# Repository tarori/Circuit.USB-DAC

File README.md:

USB Audio DAC version 10
 * Input: USB Audio class 2.0 (192kHz/24bit)
 * Output: Headphone and speakers (max 5W @8Ω)
 * THD+N < -100dB (0.001%) at 1W 8Ω 
 * Low output noise: <10uVrms (20-20kHz)
 * 4-layer PCB with solid ground
 * SDR-Widget with very low jitter design
 * Isolated USB input
 * AK4493 with AK1110 and [LED regulators](https://github.com/tarori/Circuit.LEC-Regulator) (discrete low noise, low impedance regulator) 
 * Low gain class-AB amplifier
 * Two mute relays for headphone and speakers
 * Input power: ±20V 2A

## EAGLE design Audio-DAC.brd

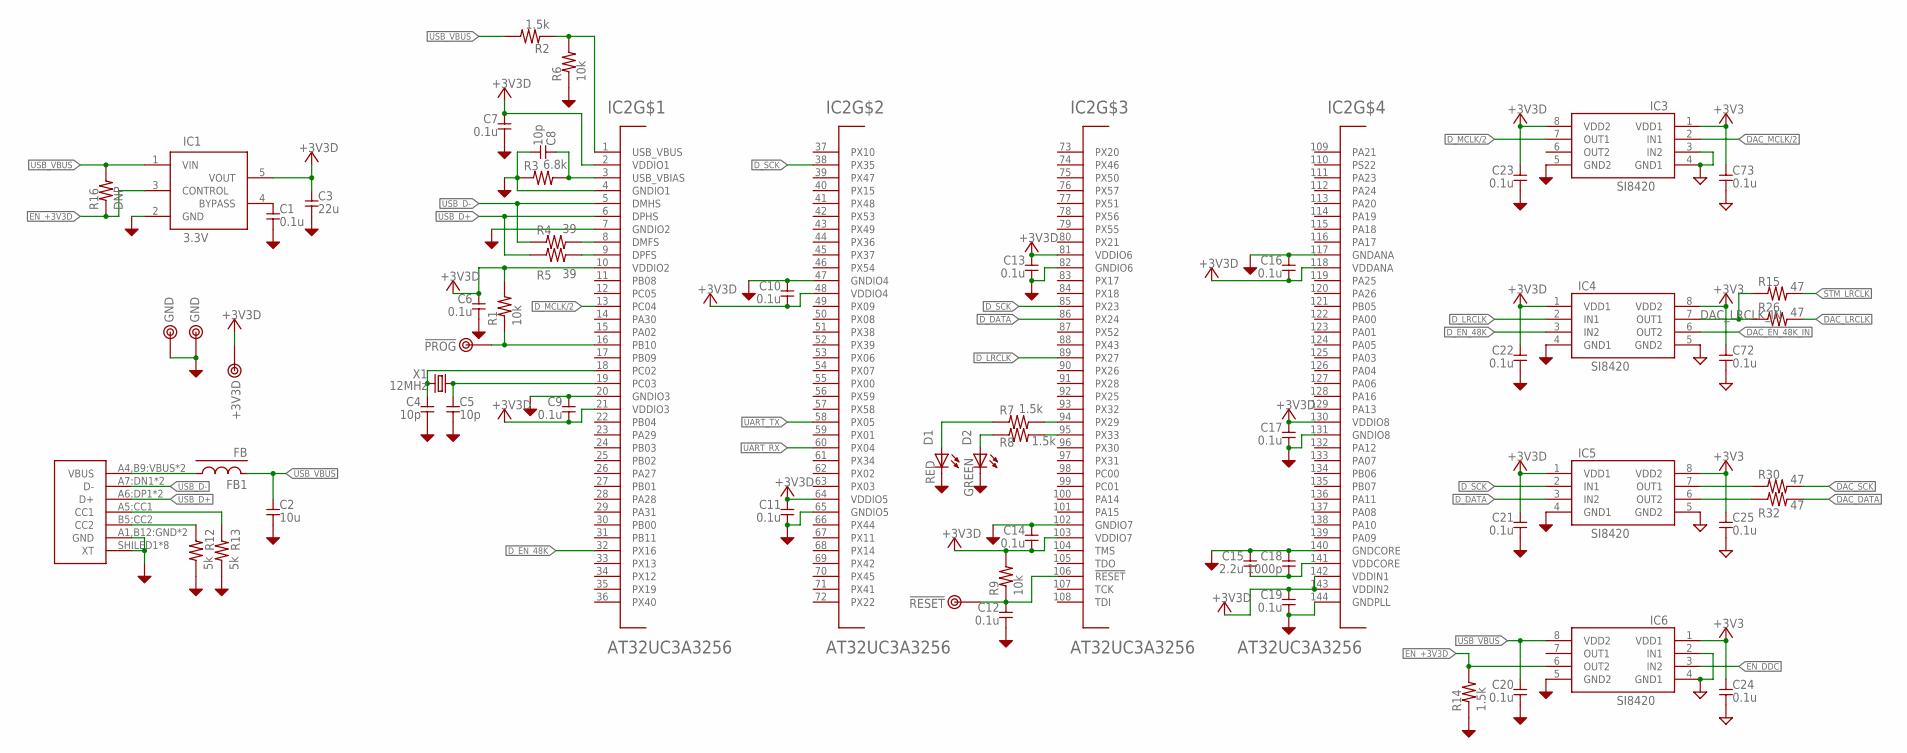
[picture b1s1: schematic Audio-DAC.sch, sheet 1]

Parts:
C1, C6, C7, C9, C10, C11, C12, C13, C14, C16, C17, C19, C20, C21, C22, C23, C24, C25, C72, C73: 0.1u; 1608C
C2: 10u; 2012
C3: 22u; 2012
C4, C5, C8: 10p; 1608C
C15: 2.2u; 2012
C18: 1000p; 1608C
CON1: USB-C; 5077CR-16-SMC2-BK-TR
D1: RED; D1608
D2: GREEN; D1608
FB1: FB; 1608-J
IC1: 3.3V; SOT23-5
IC2: AT32UC3A3256; TQFP144
IC3, IC4, IC5, IC6: SI8420; SOP8
R1, R6, R9: 10k; 1608
R2, R7, R8, R14: 1.5k; 1608
R3: 6.8k; 1608
R4, R5: 39; 1608
R12, R13: 5k; 1608
R15, R26, R30, R32: 47; 1608-J
R16: DNP; 1608-J
TP1: !PROG; TESTPIN
TP2: !RESET; TESTPIN
TP3, TP25: GND; TESTPIN
TP26: +3V3D; TESTPIN
X1: 12MHz; HC49/S

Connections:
+3V3: C24.1, C25.1, C72.1, C73.1, IC3.1 (VDD1), IC4.8 (VDD2), IC5.8 (VDD2), IC6.1 (VDD1); also elsewhere on the board
+3V3D: C3.1, C6.1, C7.1, C9.2, C10.2, C11.1, C13.1, C14.2, C16.2, C17.1, C19.1, C21.1, C22.1, C23.1, IC1.5 (VOUT), IC2.2 (VDDIO1), IC2.10 (VDDIO2), IC2.21 (VDDIO3), IC2.48 (VDDIO4), IC2.64 (VDDIO5), IC2.81 (VDDIO6), IC2.103 (VDDIO7), IC2.118 (VDDANA), IC2.130 (VDDIO8), IC2.142 (VDDIN1), IC2.143 (VDDIN2), IC3.8 (VDD2), IC4.1 (VDD1), IC5.1 (VDD1), R1.2, R9.2, TP26.1
AVR_PROG: IC2.16 (PB10), R1.1, TP1.1
DAC_DATA: R32.2; also elsewhere on the board
DAC_EN_48K_IN: IC4.6 (OUT2); also elsewhere on the board
DAC_LRCLK: R26.2; also elsewhere on the board
DAC_LRCLK_IN: IC4.7 (OUT1), R15.1, R26.1
DAC_MCLK/2: IC3.2 (IN1); also elsewhere on the board
DAC_SCK: R30.2; also elsewhere on the board
DGND: C1.2, C2.2, C3.2, C4.2, C5.2, C6.2, C7.2, C8.2, C9.1, C10.1, C11.2, C12.2, C13.2, C14.1, C15.1, C16.1, C17.2, C18.1, C19.2, C20.2, C21.2, C22.2, C23.2, CON1.A1,B12:GND (GND), CON1.B1,A12:GND (GND), CON1.SHILED1 (XT), CON1.SHILED2 (XT), CON1.SHILED3 (XT), CON1.SHILED4 (XT), CON1.SHILED5 (XT), CON1.SHILED6 (XT), CON1.SHILED7 (XT), CON1.SHILED8 (XT), D1.K, D2.K, IC1.2 (GND), IC2.4 (GNDIO1), IC2.7 (GNDIO2), IC2.20 (GNDIO3), IC2.47 (GNDIO4), IC2.65 (GNDIO5), IC2.82 (GNDIO6), IC2.102 (GNDIO7), IC2.117 (GNDANA), IC2.131 (GNDIO8), IC2.140 (GNDCORE), IC2.144 (GNDPLL), IC3.5 (GND2), IC4.4 (GND1), IC5.4 (GND1), IC6.5 (GND2), R3.1, R6.1, R12.1, R13.1, R14.1, TP3.1, TP25.1
D_!RST: C12.1, IC2.106 (!RESET), R9.1, TP2.1
D_DATA: IC2.86 (PX24), IC5.3 (IN2)
D_EN_48K: IC2.32 (PX16), IC4.3 (IN2)
D_LRCLK: IC2.89 (PX27), IC4.2 (IN1)
D_MCLK/2: IC2.13 (PC04), IC3.7 (OUT1)
D_SCK: IC2.38 (PX35), IC2.85 (PX23), IC5.2 (IN1)
EN_+3V3D: IC1.3 (CONTROL), IC6.6 (OUT2), R14.2, R16.1
EN_DDC: IC6.3 (IN2); also elsewhere on the board
GND: C24.2, C25.2, C72.2, C73.2, IC3.3 (IN2), IC3.4 (GND1), IC4.5 (GND2), IC5.5 (GND2), IC6.2 (IN1), IC6.4 (GND1); also elsewhere on the board
LED_GREEN: IC2.95 (PX33), R8.2
LED_RED: IC2.94 (PX29), R7.2
unnamed: IC2.8 (DMFS), R4.2
unnamed: IC2.9 (DPFS), R5.2
unnamed: C5.1, IC2.19 (PC03), X1.1
unnamed: C4.1, IC2.18 (PC02), X1.2
unnamed: C8.1, IC2.3 (USB_VBIAS), R3.2
unnamed: IC2.1 (USB_VBUS), R2.1, R6.2
unnamed: D2.A, R8.1
unnamed: C15.2, C18.2, IC2.141 (VDDCORE)
unnamed: D1.A, R7.1
unnamed: IC5.7 (OUT1), R30.1
unnamed: C1.1, IC1.4 (BYPASS)
unnamed: CON1.B5:CC2 (CC2), R12.2
unnamed: CON1.A5:CC1 (CC1), R13.2
unnamed: IC5.6 (OUT2), R32.1
STM_LRCLK: R15.2; also elsewhere on the board
UART_RX: IC2.60 (PX04)
UART_TX: IC2.58 (PX05)
USB_D+: CON1.A6:DP1 (D+), CON1.B6:DP2 (D+), IC2.6 (DPHS), R5.1
USB_D-: CON1.A7:DN1 (D-), CON1.B7:DN2 (D-), IC2.5 (DMHS), R4.1
USB_VBUS: C2.1, C20.1, FB1.2, IC1.1 (VIN), IC6.8 (VDD2), R2.2, R16.2
VBUS: CON1.A4,B9:VBUS (VBUS), CON1.B4,A9:VBUS (VBUS), FB1.1

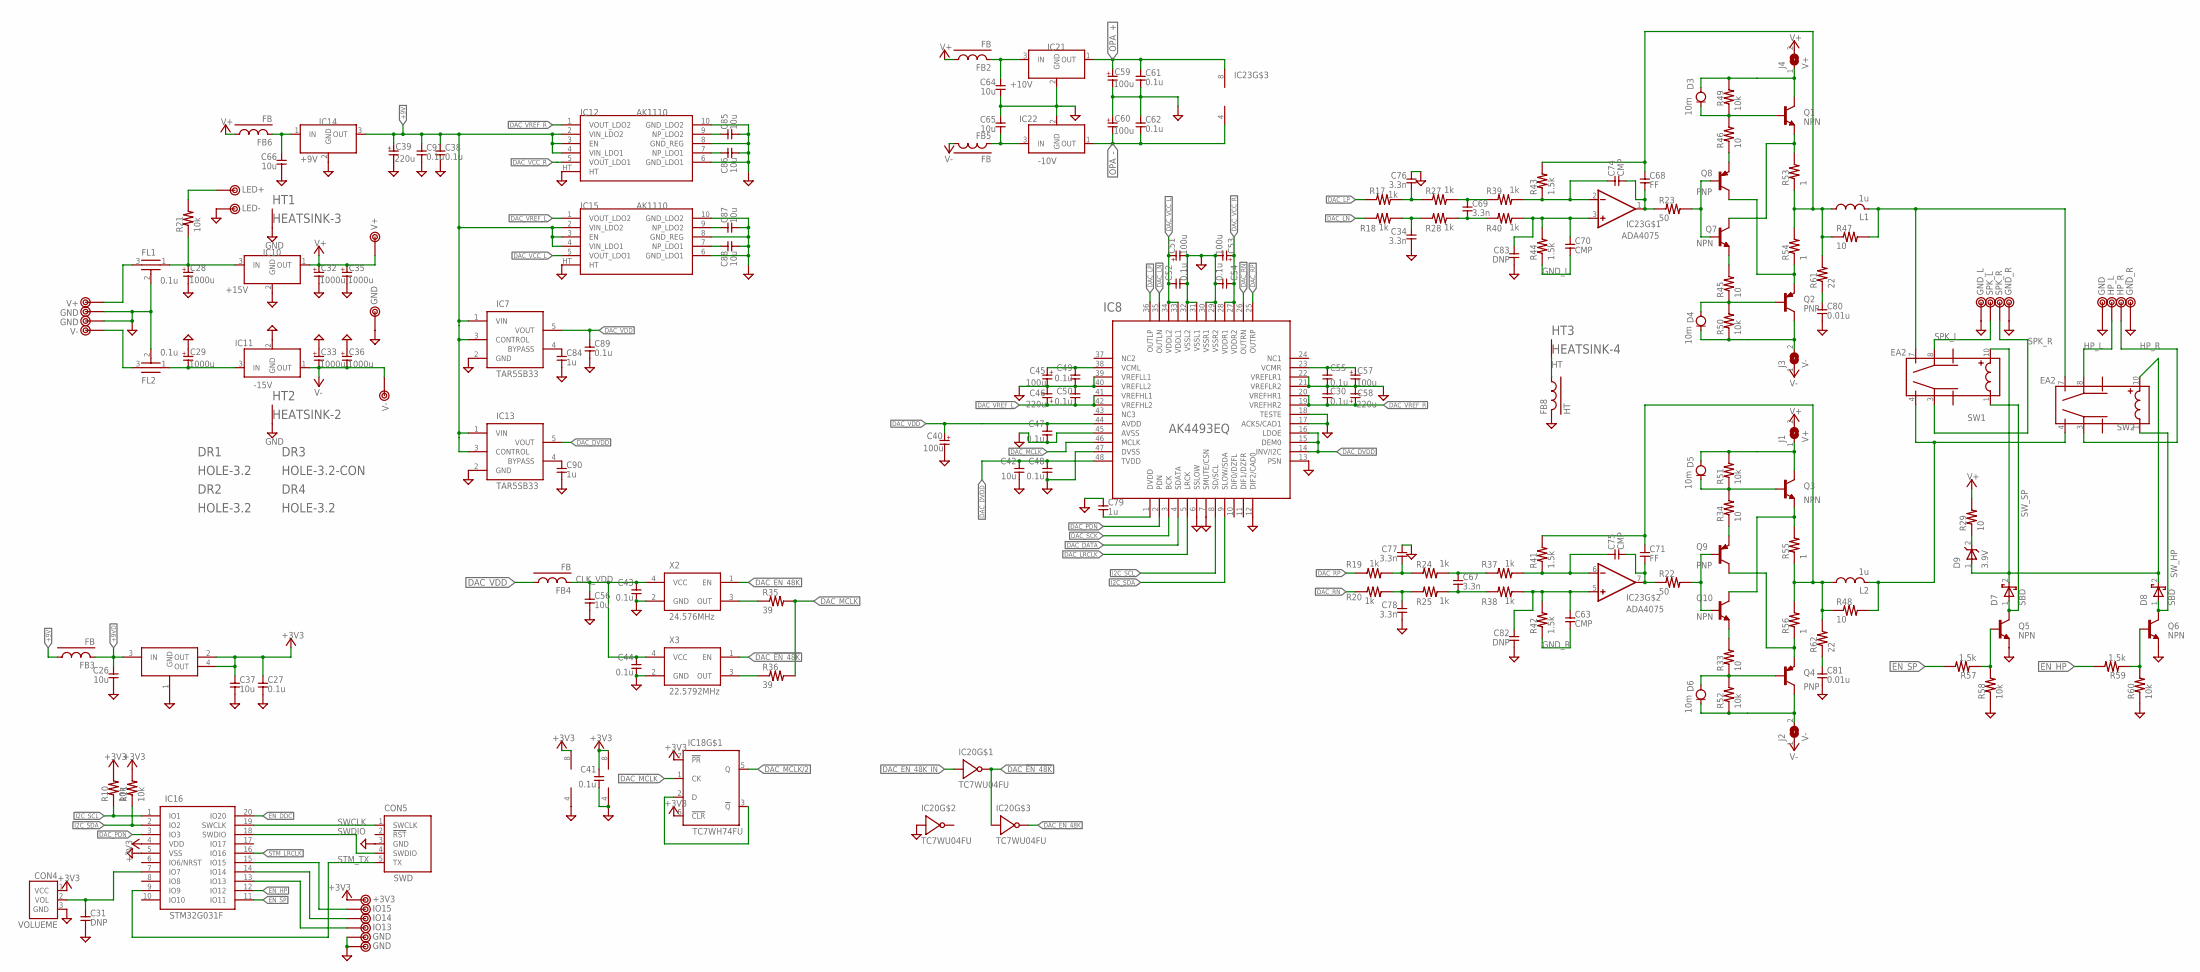
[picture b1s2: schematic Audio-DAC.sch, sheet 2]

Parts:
C26, C37, C42, C56, C64, C65, C66, C85, C86, C87, C88: 10u; 2012
C27, C30, C38, C41, C43, C44, C47, C48, C49, C50, C52, C54, C55, C61, C62, C89, C91: 0.1u; 1608C
C28, C29: 1000u; E5-13
C31, C82, C83: DNP; 1608C
C32, C33, C35, C36: 1000u; E5-10
C34, C67, C69, C76, C77, C78: 3.3n; 1608C
C39: 220u; E2,5-8
C40, C45, C51, C53, C57: 100u; E2.5-6.5
C46, C58: 220u; E2.5-6.5
C59, C60: 100u; E2,5-8
C63, C70, C74, C75: CMP; 1608C
C68, C71: FF; 1608C
C79, C84, C90: 1u; 1608C
C80, C81: 0.01u; 2012
CON4: VOLUEME; VOL_CON
CON5: SWD; SWD_CON
D3, D4, D5, D6: 10m; SOD123
D7, D8: SBD; SOD123
D9: 3.9V; SOD123
DR1, DR2, DR4: HOLE-3.2; HOLE_3.2
DR3: HOLE-3.2-CON; HOLE_3.2_CON
FB2, FB3, FB4, FB5, FB6: FB; 1608-J
FB8: HT; 2012-J
FL1, FL2: 0.1u; FL1
HT1: HEATSINK-3; HEATSINK3
HT2: HEATSINK-2; HEATSINK2
HT3: HEATSINK-4; HEATSINK4
IC7, IC13: TAR5SB33; SOT23-5
IC8: AK4493EQ; LQFP48
IC9: AZ1086H-3.3; SOT223
IC10: +15V; REGULATOR_LED
IC11: -15V; REGULATOR_LED
IC12, IC15: AK1110; PLP10-SMD
IC14: +9V; TO-220
IC16: STM32G031F; TSSOP20
IC18: TC7WH74FU; SSOP8-P-0.65
IC20: TC7WU04FU; SSOP8-P-0.65
IC21: +10V; REGULATOR_LED
IC22: -10V; REGULATOR_LED
IC23: ADA4075; SOP8
J1, J4: V+; 2012-J
J2, J3: V-; 2012-J
L1, L2: 1u; L7-10-2
Q1, Q3: NPN; TO126
Q2, Q4: PNP; TO126
Q5, Q6, Q7, Q10: NPN; SC59
Q8, Q9: PNP; SC59
R10, R11, R49, R50, R51, R52, R58, R60: 10k; 1608
R17, R18, R19, R20, R24, R25, R27, R28, R37, R38, R39, R40: 1k; 1608
R21: 10k; 2012
R22, R23: 50; 1608
R29, R47, R48: 10; 2012
R33, R34, R45, R46: 10; 1608
R35, R36: 39; 1608-J
R41, R42, R43, R44, R57, R59: 1.5k; 1608
R53, R55, R56: 1; 0207/2V
R54: 1; 0204/5
R61, R62: 22; 2012
SW1, SW2: EA2
TP5, TP11: V+; TESTPIN-BIG
TP6, TP7, TP22, TP31: GND; TESTPIN-BIG
TP8, TP21: V-; TESTPIN-BIG
TP9: IO15; TESTPIN
TP10: IO14; TESTPIN
TP12: IO13; TESTPIN
TP13, TP14: GND; TESTPIN
TP15: LED+; TESTPIN
TP16: LED-; TESTPIN
TP17: +3V3; TESTPIN
TP27: GND_L; TESTPIN-BIG
TP28: SPK_L; TESTPIN-BIG
TP29: SPK_R; TESTPIN-BIG
TP30, TP34: GND_R; TESTPIN-BIG
TP32: HP_L; TESTPIN-BIG
TP33: HP_R; TESTPIN-BIG
X2: 24.576MHz; KC3225
X3: 22.5792MHz; KC3225

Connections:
+3V3: C27.1, C37.1, C41.1, CON4.1 (VCC), IC9.2 (OUT), IC9.4 (OUT), IC16.4 (VDD), IC18.6 (!CLR), IC18.7 (!PR), IC18.8 (V+), IC20.8 (V+), R10.2, R11.2, TP17.1; also elsewhere on the board
+9V: C38.1, C39.+ (1), C91.1, FB3.1, IC7.1 (VIN), IC7.3 (CONTROL), IC12.2 (VIN_LDO2), IC12.3 (EN), IC12.4 (VIN_LDO1), IC13.1 (VIN), IC13.3 (CONTROL), IC14.3 (OUT), IC15.2 (VIN_LDO2), IC15.3 (EN), IC15.4 (VIN_LDO1)
+9VD: C26.1, FB3.2, IC9.3 (IN)
+12V: D7.2 (K), D8.2 (K), D9.1 (A), SW1.10 (L2), SW2.10 (L2)
AMP_LOUT: C68.1, L1.1, R43.2, R47.1, R53.1, R54.2, R61.2
AMP_ROUT: C71.1, L2.1, R41.2, R48.1, R55.1, R56.2, R62.2
CLK_VDD: C43.1, C44.1, C56.1, FB4.2, X2.4 (VCC), X3.4 (VCC)
DAC_!EN_48K: IC20.3 (IN), IC20.7 (OUT), X3.1 (EN)
DAC_DATA: IC8.4 (SDATA); also elsewhere on the board
DAC_DVDD: C42.1, C48.1, IC8.14 (INV/I2C), IC8.15 (DEM0), IC8.16 (LDOE), IC8.48 (TVDD), IC13.5 (VOUT)
DAC_EN_48K: IC20.5 (OUT), X2.1 (EN)
DAC_EN_48K_IN: IC20.1 (IN); also elsewhere on the board
DAC_LN: IC8.35 (OUTLN), R18.1
DAC_LP: IC8.36 (OUTLP), R17.1
DAC_LRCLK: IC8.5 (LRCK); also elsewhere on the board
DAC_MCLK: IC8.46 (MCLK), IC18.1 (CK), R35.2, R36.2
DAC_MCLK/2: IC18.5 (Q); also elsewhere on the board
DAC_PDN: IC8.2 (PDN), IC16.3 (IO3)
DAC_RN: IC8.26 (OUTRN), R20.1
DAC_RP: IC8.25 (OUTRP), R19.1
DAC_SCK: IC8.3 (BCK); also elsewhere on the board
DAC_VCC_L: C51.+ (1), C52.1, IC8.33 (VDDL1), IC8.34 (VDDL2), IC15.5 (VOUT_LDO1)
DAC_VCC_R: C53.+ (1), C54.1, IC8.27 (VDDR2), IC8.28 (VDDR1), IC12.5 (VOUT_LDO1)
DAC_VDD: C40.+ (1), C47.1, C89.1, FB4.1, IC7.5 (VOUT), IC8.44 (AVDD)
DAC_VREF_L: C46.+ (1), C50.2, IC8.41 (VREFHL1), IC8.42 (VREFHL2), IC15.1 (VOUT_LDO2)
DAC_VREF_R: C30.2, C58.+ (1), IC8.19 (VREFHR2), IC8.20 (VREFHR1), IC12.1 (VOUT_LDO2)
EN_DDC: IC16.20 (IO20); also elsewhere on the board
EN_HP: IC16.12 (IO12), R59.2
EN_SP: IC16.11 (IO11), R57.2
GND: C26.2, C27.2, C28.- (2), C29.+ (1), C30.1, C31.2, C32.- (2), C33.+ (1), C34.2, C35.- (2), C36.+ (1), C37.2, C38.2, C39.- (2), C40.- (2), C41.2, C42.2, C43.2, C44.2, C45.- (2), C46.- (2), C47.2, C48.2, C49.2, C50.1, C51.- (2), C52.2, C53.- (2), C54.2, C55.2, C56.2, C57.- (2), C58.- (2), C59.- (2), C60.+ (1), C61.2, C62.1, C64.2, C65.1, C66.2, C76.1, C77.1, C78.2, C79.1, C80.2, C81.2, C82.2, C83.2, C84.2, C85.2, C86.2, C87.2, C88.2, C89.2, C90.2, C91.2, CON4.3 (GND), CON5.3 (GND), FB8.2, FL1.2 (GND), FL2.2 (GND), HT1.HT1, HT1.HT2, HT2.HT1, IC7.2 (GND), IC8.6 (SSLOW), IC8.7 (SMUTE/CSN), IC8.12 (DIF2/CAD0), IC8.13 (PSN), IC8.17 (ACKS/CAD1), IC8.18 (TESTE), IC8.21 (VREFLR2), IC8.22 (VREFLR1), IC8.29 (VSSR2), IC8.30 (VSSR1), IC8.31 (VSSL1), IC8.32 (VSSL2), IC8.39 (VREFLL1), IC8.40 (VREFLL2), IC8.45 (AVSS), IC8.47 (DVSS), IC9.1 (GND), IC10.2 (GND), IC11.2 (GND), IC12.6 (GND_LDO1), IC12.8 (GND_REG), IC12.10 (GND_LDO2), IC12.HT, IC13.2 (GND), IC14.2 (GND), IC15.6 (GND_LDO1), IC15.8 (GND_REG), IC15.10 (GND_LDO2), IC15.HT, IC16.5 (VSS), IC18.4 (V-), IC20.4 (V-), IC20.6 (IN), IC21.2 (GND), IC22.2 (GND), Q5.2 (E), Q6.2 (E), R58.1, R60.1, TP6.1, TP7.1, TP13.1, TP14.1, TP16.1, TP22.1, TP27.1, TP30.1, TP31.1, TP34.1, X2.2 (GND), X3.2 (GND); also elsewhere on the board
GND_L: C70.2, R44.1
GND_R: C63.2, R42.1
HP_L: SW2.8 (COM2), TP32.1
HP_R: SW2.3 (COM1), TP33.1
HT: FB8.1, HT3.HT1, HT3.HT2
I2C_SCL: IC8.8 (SD/SCL), IC16.1 (IO1), R10.1
I2C_SDA: IC8.9 (SLOW/SDA), IC16.2 (IO2), R11.1
unnamed: C84.1, IC7.4 (BYPASS)
unnamed: C86.1, IC12.7 (NP_LDO1)
unnamed: C85.1, IC12.9 (NP_LDO2)
unnamed: C87.1, IC15.9 (NP_LDO2)
unnamed: D4.1 (A), Q2.3 (B), R45.1, R50.2
unnamed: C90.1, IC13.4 (BYPASS)
unnamed: C64.1, FB2.2, IC21.3 (IN)
unnamed: C75.1, IC23.6 (-IN), R37.2, R41.1
unnamed: C63.1, C82.1, IC23.5 (+IN), R38.2, R42.2
unnamed: C65.2, FB5.2, IC22.3 (IN)
unnamed: C66.1, FB6.2, IC14.1 (IN)
unnamed: Q3.1 (E), Q10.3 (C), R55.2
unnamed: Q9.1 (B), Q10.1 (B), R22.2
unnamed: C69.1, R27.2, R39.1
unnamed: Q4.1 (E), Q9.3 (C), R56.1
unnamed: Q9.2 (E), R34.1
unnamed: Q2.1 (E), Q8.3 (C), R54.1
unnamed: Q1.1 (E), Q7.3 (C), R53.2
unnamed: L2.2, R48.2, SW1.4 (A1), SW2.4 (A1)
unnamed: L1.2, R47.2, SW1.7 (A2), SW2.7 (A2)
unnamed: Q5.1 (B), R57.1, R58.2
unnamed: IC16.13 (IO13), TP12.1
unnamed: C69.2, R28.2, R40.1
unnamed: IC16.14 (IO14), TP10.1
unnamed: FL1.3 (IN), TP5.1
unnamed: FL2.3 (IN), TP8.1
unnamed: C77.2, R19.2, R24.1
unnamed: C78.1, R20.2, R25.1
unnamed: R21.2, TP15.1
unnamed: C74.1, IC23.2 (-IN), R39.2, R43.1
unnamed: C70.1, C83.1, IC23.3 (+IN), R40.2, R44.2
unnamed: C79.2, IC8.1 (DVDD)
unnamed: C71.2, C75.2, IC23.7 (OUT), R22.1
unnamed: Q6.1 (B), R59.1, R60.2
unnamed: D3.2 (K), Q1.3 (B), R46.2, R49.1
unnamed: C68.2, C74.2, IC23.1 (OUT), R23.1
unnamed: Q10.2 (E), R33.2
unnamed: IC16.15 (IO15), TP9.1
unnamed: Q7.1 (B), Q8.1 (B), R23.2
unnamed: D6.1 (A), Q4.3 (B), R33.1, R52.2
unnamed: D6.2 (K), J2.2, Q4.2 (C), R52.1
unnamed: D5.2 (K), Q3.3 (B), R34.2, R51.1
unnamed: Q7.2 (E), R45.2
unnamed: Q8.2 (E), R46.1
unnamed: C67.1, R24.2, R37.1
unnamed: D5.1 (A), J1.1, Q3.2 (C), R51.2
unnamed: D4.2 (K), J3.2, Q2.2 (C), R50.1
unnamed: D3.1 (A), J4.1, Q1.2 (C), R49.2
unnamed: C67.2, R25.2, R38.1
unnamed: C76.2, R17.2, R27.1
unnamed: C34.1, R18.2, R28.1
unnamed: C80.1, R61.1
unnamed: C81.1, R62.1
unnamed: C88.1, IC15.7 (NP_LDO1)
unnamed: D9.2 (C), R29.1
unnamed: C31.1, CON4.2 (VOL), IC16.7 (IO7)
unnamed: R35.1, X2.3 (OUT)
unnamed: R36.1, X3.3 (OUT)
unnamed: IC18.2 (D), IC18.3 (!Q)
OPA_+: C59.+ (1), C61.1, IC21.1 (OUT), IC23.8 (V+)
OPA_-: C60.- (2), C62.2, IC22.1 (OUT), IC23.4 (V-)
SPK_L: SW1.8 (COM2), TP28.1
SPK_R: SW1.3 (COM1), TP29.1
STM_LRCLK: IC16.16 (IO16); also elsewhere on the board
STM_TX: CON5.5 (TX), IC16.9 (IO9)
SWCLK: CON5.1 (SWCLK), IC16.19 (SWCLK)
SWDIO: CON5.4 (SWDIO), IC16.18 (SWDIO)
SW_HP: D8.1 (A), Q6.3 (C), SW2.1 (L1)
SW_SP: D7.1 (A), Q5.3 (C), SW1.1 (L1)
V+: C32.+ (1), C35.+ (1), FB2.1, FB6.1, IC10.1 (OUT), J1.2, J4.2, R29.2, TP11.1
V-: C33.- (2), C36.- (2), FB5.1, IC11.1 (OUT), J2.1, J3.1, TP21.1
VCOM_L: C45.+ (1), C49.1, IC8.38 (VCML)
VCOM_R: C55.1, C57.+ (1), IC8.23 (VCMR)
VIN+: C28.+ (1), FL1.1 (OUT), IC10.3 (IN), R21.1
VIN-: C29.- (2), FL2.1 (OUT), IC11.3 (IN)

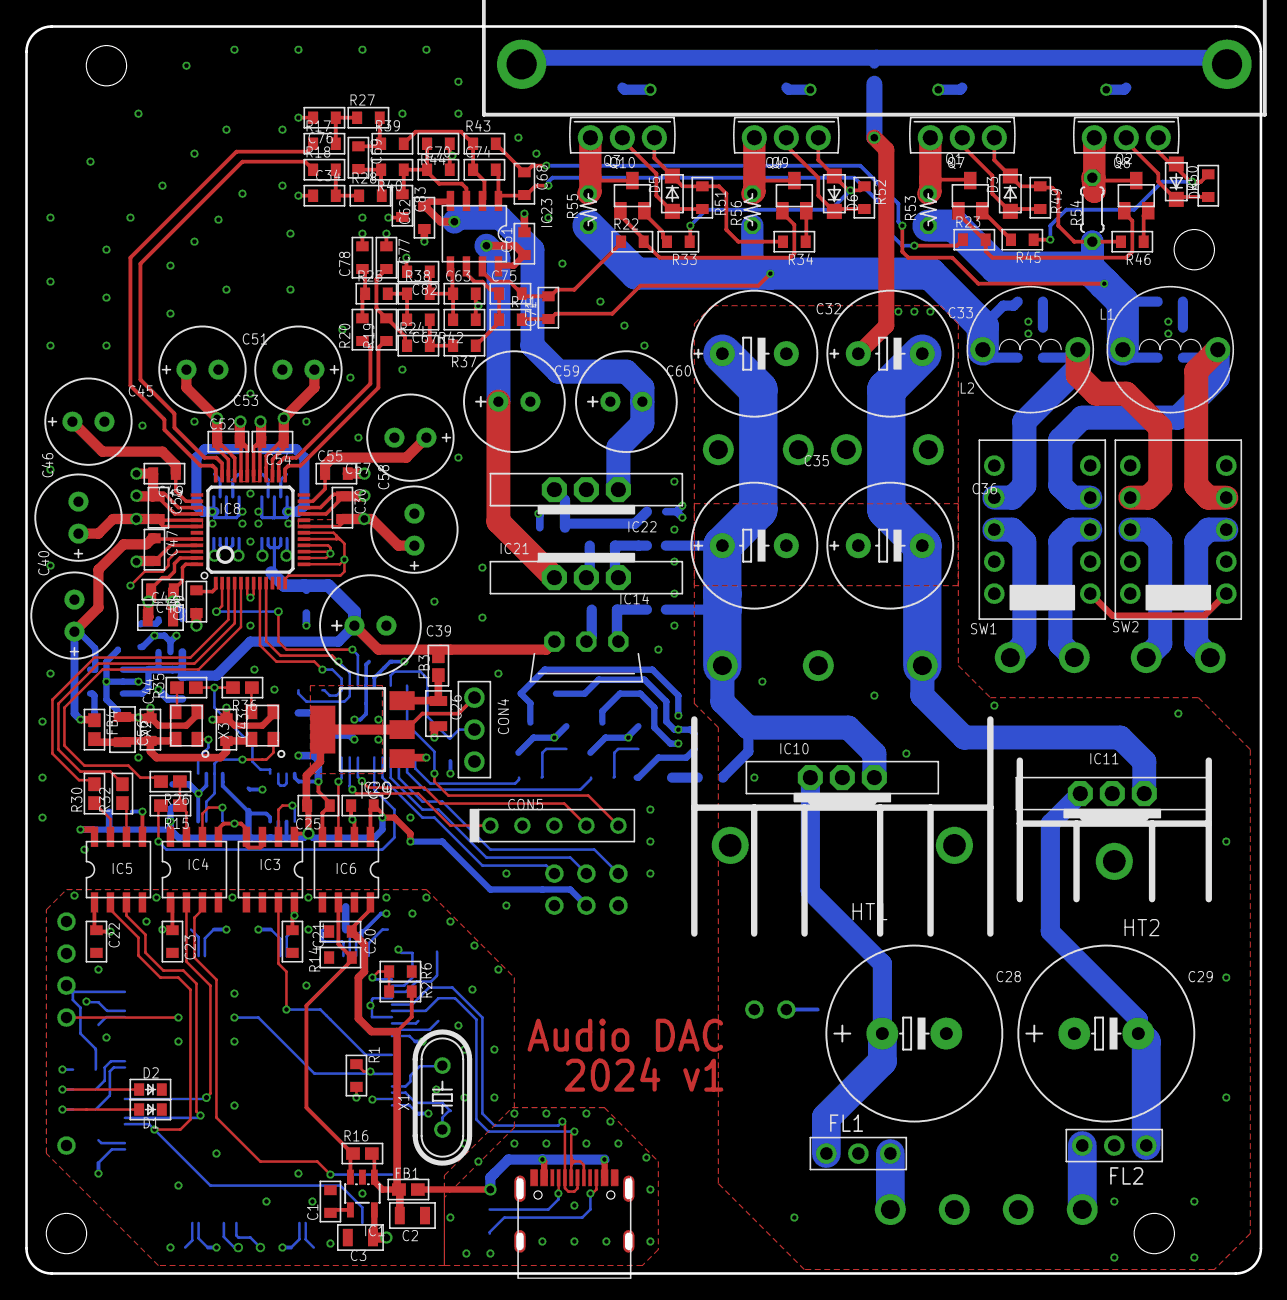
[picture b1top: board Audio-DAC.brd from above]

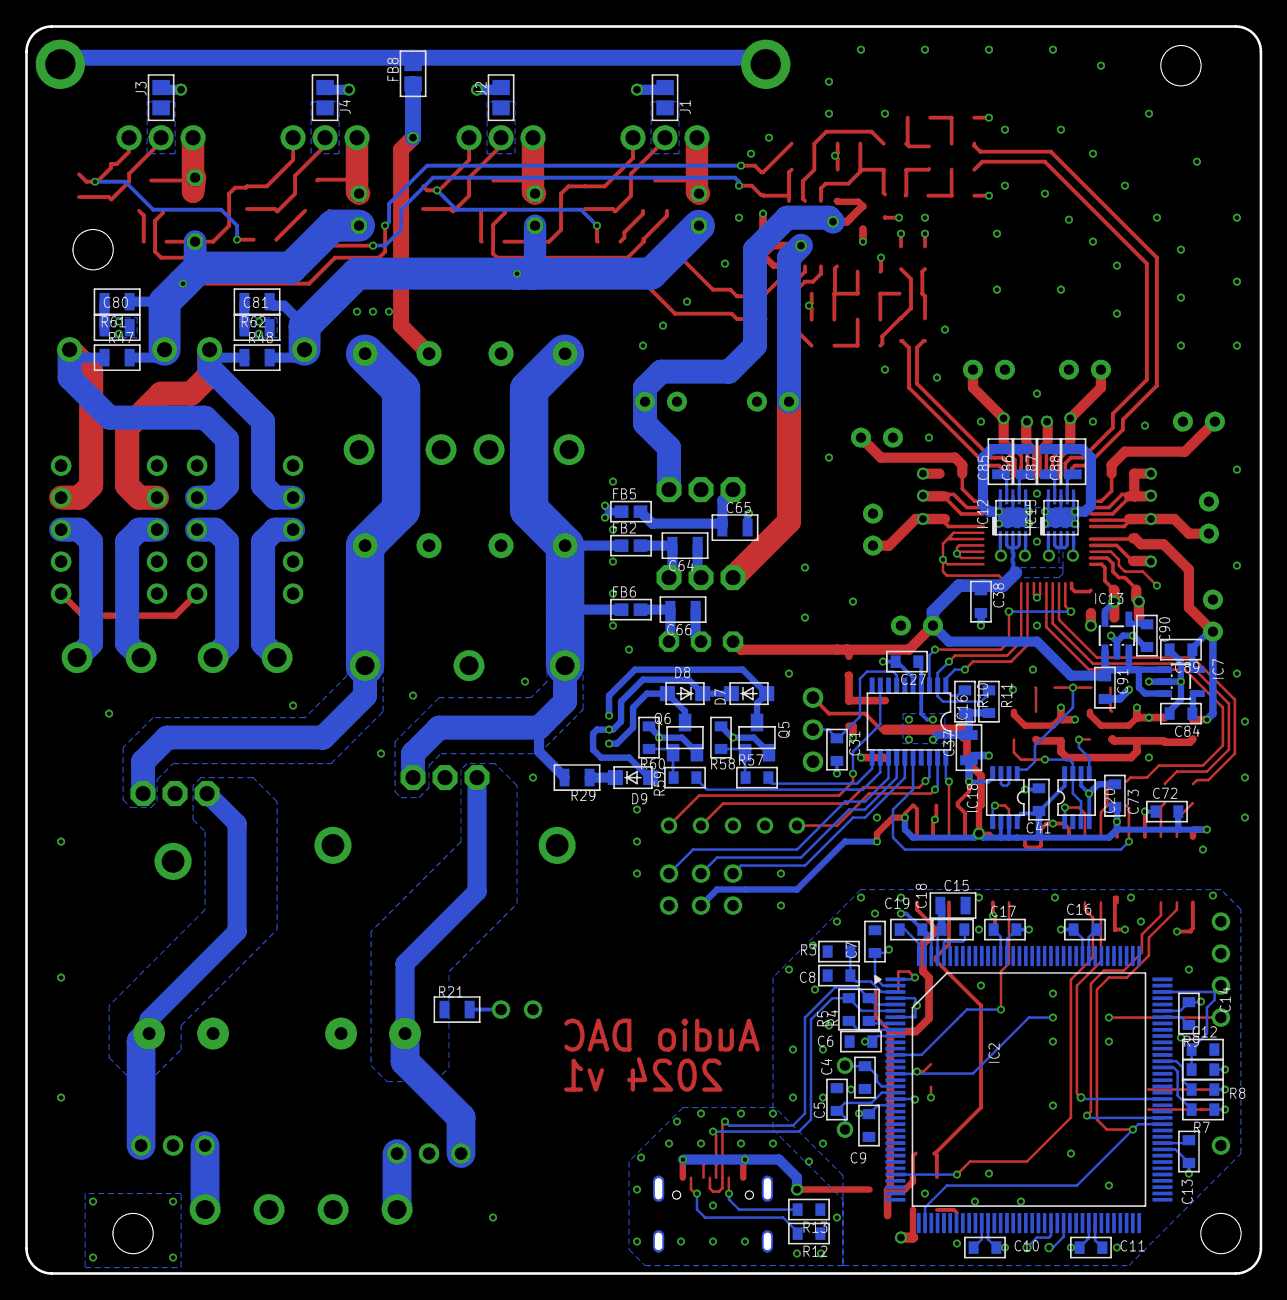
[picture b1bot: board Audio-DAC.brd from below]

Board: 4 copper layers, 98.0 x 99.0 mm, 250 parts (77 on the bottom side), 143 nets.

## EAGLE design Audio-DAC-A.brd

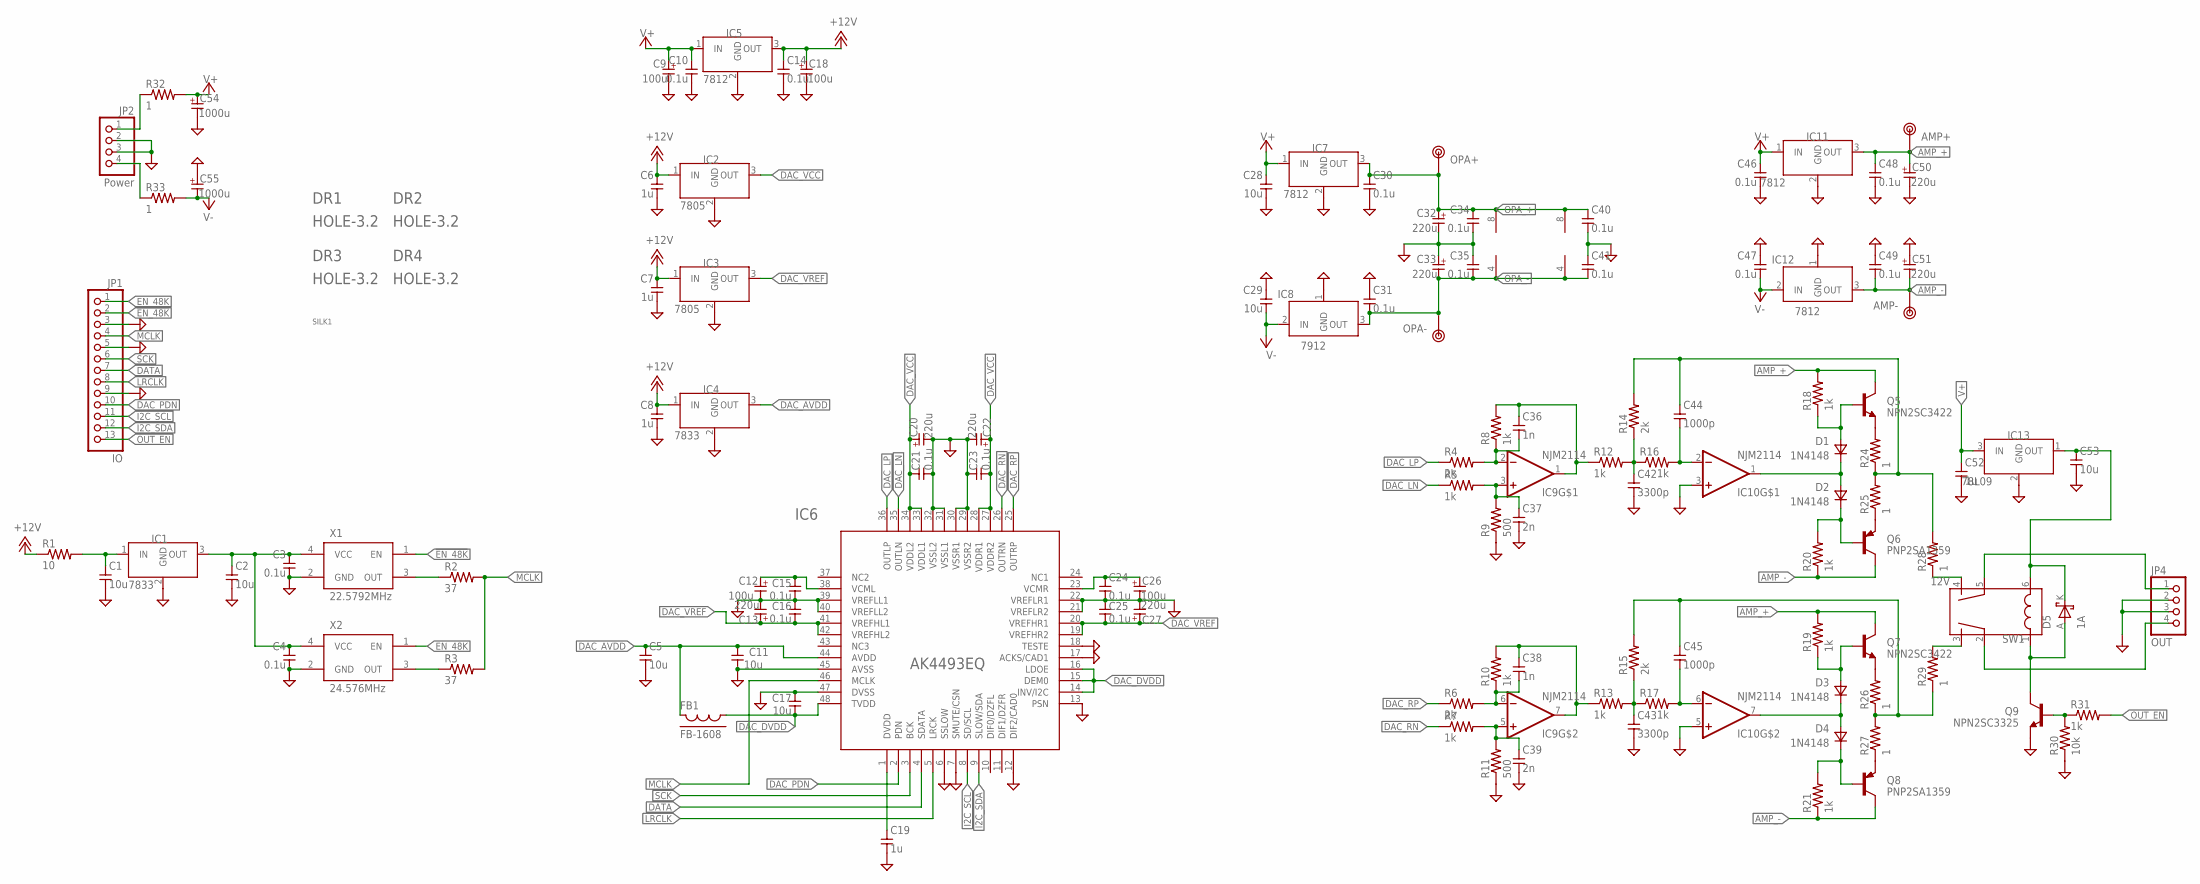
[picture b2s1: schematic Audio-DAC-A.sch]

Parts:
C1, C2, C5, C53: 10u; 2012
C3, C4, C10, C14, C15, C16, C21, C23, C24, C25, C30, C31, C34, C35, C40, C41, C46, C47, C48, C49: 0.1u; 1608
C6, C7, C8, C19, C52: 1u; 1608
C9, C18: 100u; E2,5-8
C11, C17, C28, C29: 10u; 1608
C12, C26: 100u; E2.5-6.5
C13, C20, C22, C27, C32, C33: 220u; E2.5-6.5
C36, C38: 1n; 1608
C37, C39: 2n; 1608
C42, C43: 3300p; 1608
C44, C45: 1000p; 1608
C50, C51: 220u; E5-10
C54, C55: 1000u; E5-10
D1, D2, D3, D4: 1N4148; D0207/2V
D5: 1A; TUMD2M
DR1, DR2, DR3, DR4: HOLE-3.2; HOLE_3.2
FB1: FB-1608; 1608
IC1, IC4: 7833; 7805-LARGEHOLE
IC2, IC3: 7805; 7805-LARGEHOLE
IC5, IC7, IC11, IC12: 7812; 7805-LARGEHOLE
IC6: AK4493EQ; LQFP48
IC8: 7912; 7805-LARGEHOLE
IC9, IC10: NJM2114; DIL08
IC13: 78L09; TO-92
JP1: IO; 1X13
JP2: Power; 1X04
JP4: OUT; 1X04
Q5, Q7: NPN2SC3422; TO126
Q6, Q8: PNP2SA1359; TO126
Q9: NPN2SC3325; SC59
R1: 10; 0204/7
R2, R3: 37; 1608
R4, R6, R14, R15: 2k; 0207/2V
R5, R7, R8, R10, R12, R13, R16, R17, R18, R19, R20, R21: 1k; 0207/2V
R9, R11: 500; 0207/2V
R24, R25, R26, R27, R28, R29: 1; 0207/2V
R30: 10k; 1608
R31: 1k; 0204/7
R32, R33: 1; 0207/10
SILK1: ROBOTECHWHEELSILK-9MM; ROBOTECHWHEEL-9MM
SW1: 12V; ALA2F
TP1: AMP+; TESTPIN
TP2: AMP-; TESTPIN
TP3: OPA-; TESTPIN
TP4: OPA+; TESTPIN
X1: 22.5792MHz; KC7050
X2: 24.576MHz; KC7050

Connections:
!EN_48K: JP1.2, X1.1 (EN)
+12V: C6.1, C7.1, C8.1, C14.1, C18.+ (1), IC2.1 (IN), IC3.1 (IN), IC4.1 (IN), IC5.3 (OUT), R1.1
AMP_+: C48.1, C50.+ (1), IC11.3 (OUT), Q5.2 (C), Q7.2 (C), R18.2, R19.2, TP1.1
AMP_-: C49.2, C51.- (2), IC12.3 (OUT), Q6.2 (C), Q8.2 (C), R20.1, R21.1, TP2.1
DAC_AVDD: C5.1, C11.1, FB1.2, IC4.3 (OUT), IC6.44 (AVDD)
DAC_DVDD: C17.2, FB1.1, IC6.14 (INV/I2C), IC6.15 (DEM0), IC6.16 (LDOE), IC6.48 (TVDD)
DAC_LN: IC6.35 (OUTLN), R5.1
DAC_LP: IC6.36 (OUTLP), R4.1
DAC_PDN: IC6.2 (PDN), JP1.10
DAC_RN: IC6.26 (OUTRN), R7.1
DAC_RP: IC6.25 (OUTRP), R6.1
DAC_VCC: C20.+ (1), C21.1, C22.+ (1), C23.2, IC2.3 (OUT), IC6.27 (VDDR2), IC6.28 (VDDR1), IC6.33 (VDDL1), IC6.34 (VDDL2)
DAC_VREF: C13.+ (1), C16.2, C25.2, C27.+ (1), IC3.3 (OUT), IC6.19 (VREFHR2), IC6.20 (VREFHR1), IC6.41 (VREFHL1), IC6.42 (VREFHL2)
DATA: IC6.4 (SDATA), JP1.7
EN_48K: JP1.1, X2.1 (EN)
GND: C1.2, C2.2, C3.2, C4.2, C5.2, C6.2, C7.2, C8.2, C9.- (2), C10.2, C11.2, C12.- (2), C13.- (2), C14.2, C15.2, C16.1, C17.1, C18.- (2), C19.2, C20.- (2), C21.2, C22.- (2), C23.1, C24.2, C25.1, C26.- (2), C27.- (2), C28.2, C29.1, C30.2, C31.1, C32.- (2), C33.+ (1), C34.2, C35.1, C37.2, C39.2, C40.2, C41.1, C42.2, C43.2, C46.2, C47.1, C48.2, C49.1, C50.- (2), C51.+ (1), C52.2, C53.2, C54.- (2), C55.+ (1), IC1.2 (GND), IC2.2 (GND), IC3.2 (GND), IC4.2 (GND), IC5.2 (GND), IC6.6 (SSLOW), IC6.7 (SMUTE/CSN), IC6.12 (DIF2/CAD0), IC6.13 (PSN), IC6.17 (ACKS/CAD1), IC6.18 (TESTE), IC6.21 (VREFLR2), IC6.22 (VREFLR1), IC6.29 (VSSR2), IC6.30 (VSSR1), IC6.31 (VSSL1), IC6.32 (VSSL2), IC6.39 (VREFLL1), IC6.40 (VREFLL2), IC6.45 (AVSS), IC6.47 (DVSS), IC7.2 (GND), IC8.1 (GND), IC10.3 (+IN), IC10.5 (+IN), IC11.2 (GND), IC12.1 (GND), IC13.2 (GND), JP1.3, JP1.5, JP1.9, JP2.2, JP2.3, JP4.2, JP4.3, Q9.2 (E), R9.1, R11.1, R30.1, X1.2 (GND), X2.2 (GND)
I2C_SCL: IC6.8 (SD/SCL), JP1.11
I2C_SDA: IC6.9 (SLOW/SDA), JP1.12
LRCLK: IC6.5 (LRCK), JP1.8
MCLK: IC6.46 (MCLK), JP1.4, R2.2, R3.2
unnamed: JP2.1, R32.1
unnamed: JP2.4, R33.1
unnamed: C39.1, IC9.5 (+IN), R7.2, R11.2
unnamed: D3.1 (A), Q7.3 (B), R19.1
unnamed: D3.2 (K), D4.1 (A), IC10.7 (OUT)
unnamed: D4.2 (K), Q8.3 (B), R21.2
unnamed: C12.+ (1), C15.1, IC6.38 (VCML)
unnamed: R29.2, SW1.3 (A1)
unnamed: Q7.1 (E), R26.2
unnamed: C38.2, IC9.6 (-IN), R6.2, R10.1
unnamed: C19.1, IC6.1 (DVDD)
unnamed: C24.1, C26.+ (1), IC6.23 (VCMR)
unnamed: Q8.1 (E), R27.1
unnamed: C45.1, R15.2, R26.1, R27.2, R29.1
unnamed: Q6.1 (E), R25.1
unnamed: Q5.1 (E), R24.2
unnamed: C44.1, R14.2, R24.1, R25.2, R28.2
unnamed: C38.1, IC9.7 (OUT), R10.2, R13.1
unnamed: C37.1, IC9.3 (+IN), R5.2, R9.2
unnamed: C36.2, IC9.2 (-IN), R4.2, R8.1
unnamed: C36.1, IC9.1 (OUT), R8.2, R12.1
unnamed: C42.1, R12.2, R14.1, R16.1
unnamed: C43.1, R13.2, R15.1, R17.1
unnamed: C45.2, IC10.6 (-IN), R17.2
unnamed: C44.2, IC10.2 (-IN), R16.2
unnamed: D1.1 (A), Q5.3 (B), R18.1
unnamed: R28.1, SW1.4 (A2)
unnamed: C53.1, D5.K, IC13.1 (OUT), SW1.6 (L2)
unnamed: D2.2 (K), Q6.3 (B), R20.2
unnamed: JP4.4, SW1.2 (COM1)
unnamed: D5.A, Q9.3 (C), SW1.1 (L1)
unnamed: JP4.1, SW1.5 (COM2)
unnamed: Q9.1 (B), R30.2, R31.1
unnamed: D1.2 (K), D2.1 (A), IC10.1 (OUT)
unnamed: R2.1, X1.3 (OUT)
unnamed: R3.1, X2.3 (OUT)
unnamed: C1.1, IC1.1 (IN), R1.2
OPA_+: C30.1, C32.+ (1), C34.1, C40.1, IC7.3 (OUT), IC9.8 (V+), IC10.8 (V+), TP4.1
OPA_-: C31.2, C33.- (2), C35.2, C41.2, IC8.3 (OUT), IC9.4 (V-), IC10.4 (V-), TP3.1
OUT_EN: JP1.13, R31.2
SCK: IC6.3 (BCK), JP1.6
V+: C9.+ (1), C10.1, C28.1, C46.1, C52.1, C54.+ (1), IC5.1 (IN), IC7.1 (IN), IC11.1 (IN), IC13.3 (IN), R32.2
V-: C29.2, C47.2, C55.- (2), IC8.2 (IN), IC12.2 (IN), R33.2
XTAL_VCC: C2.1, C3.1, C4.1, IC1.3 (OUT), X1.4 (VCC), X2.4 (VCC)

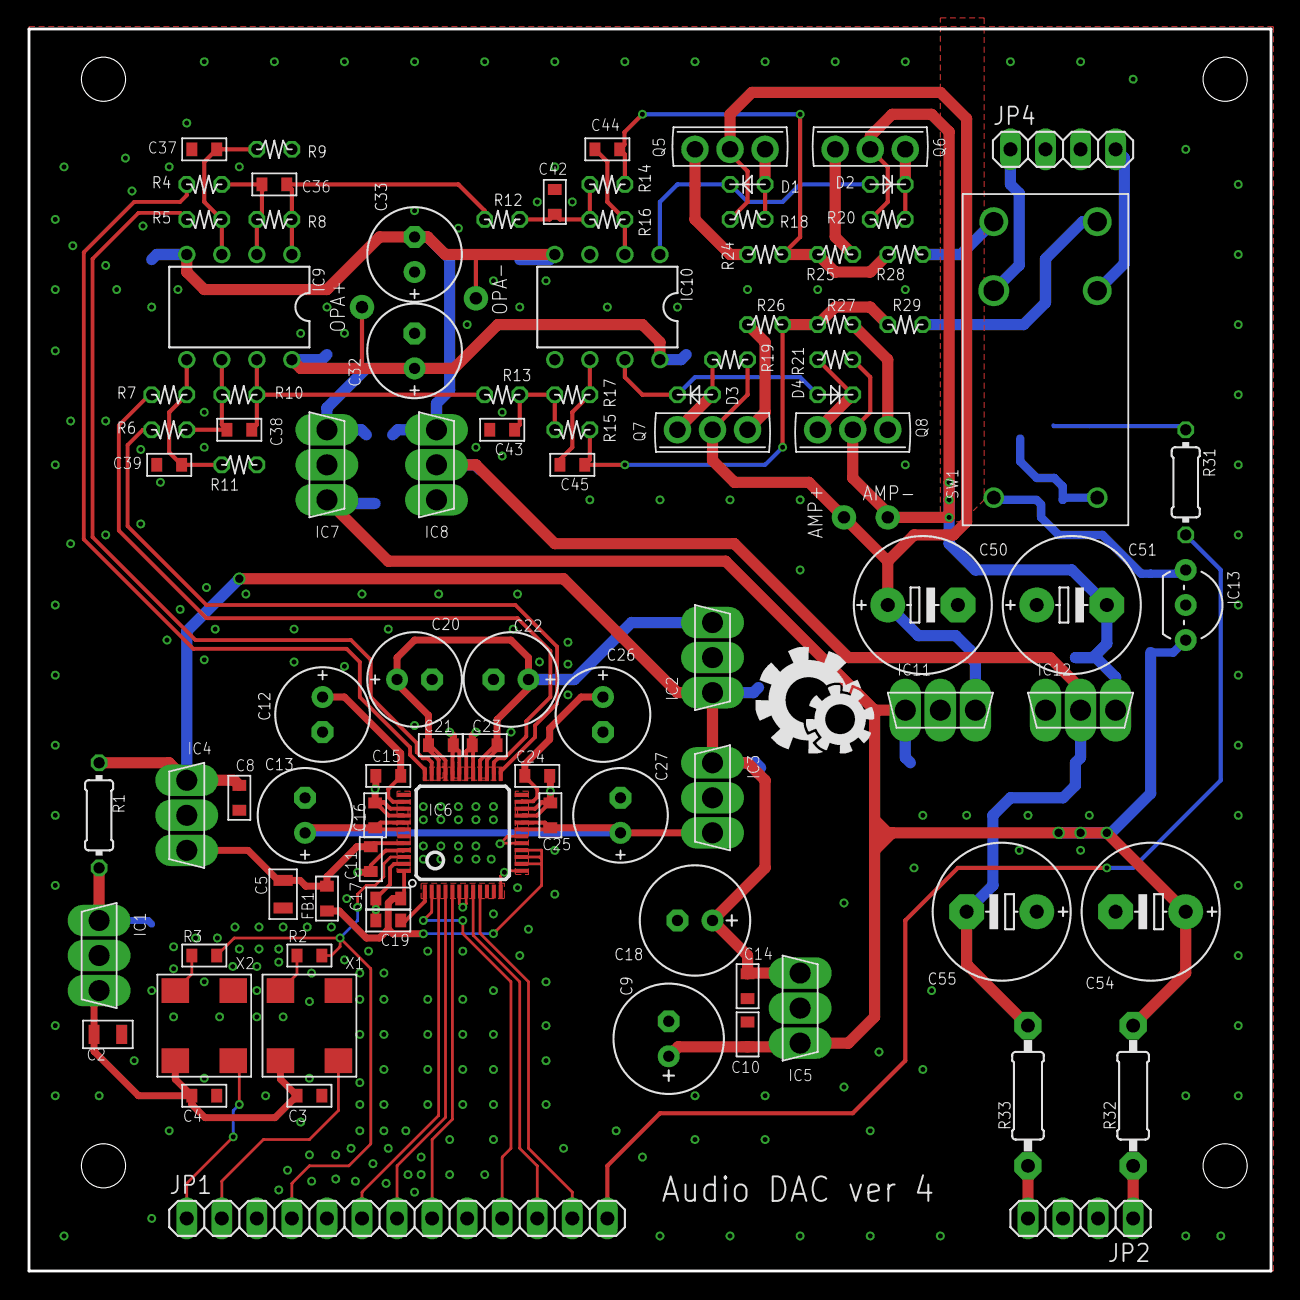
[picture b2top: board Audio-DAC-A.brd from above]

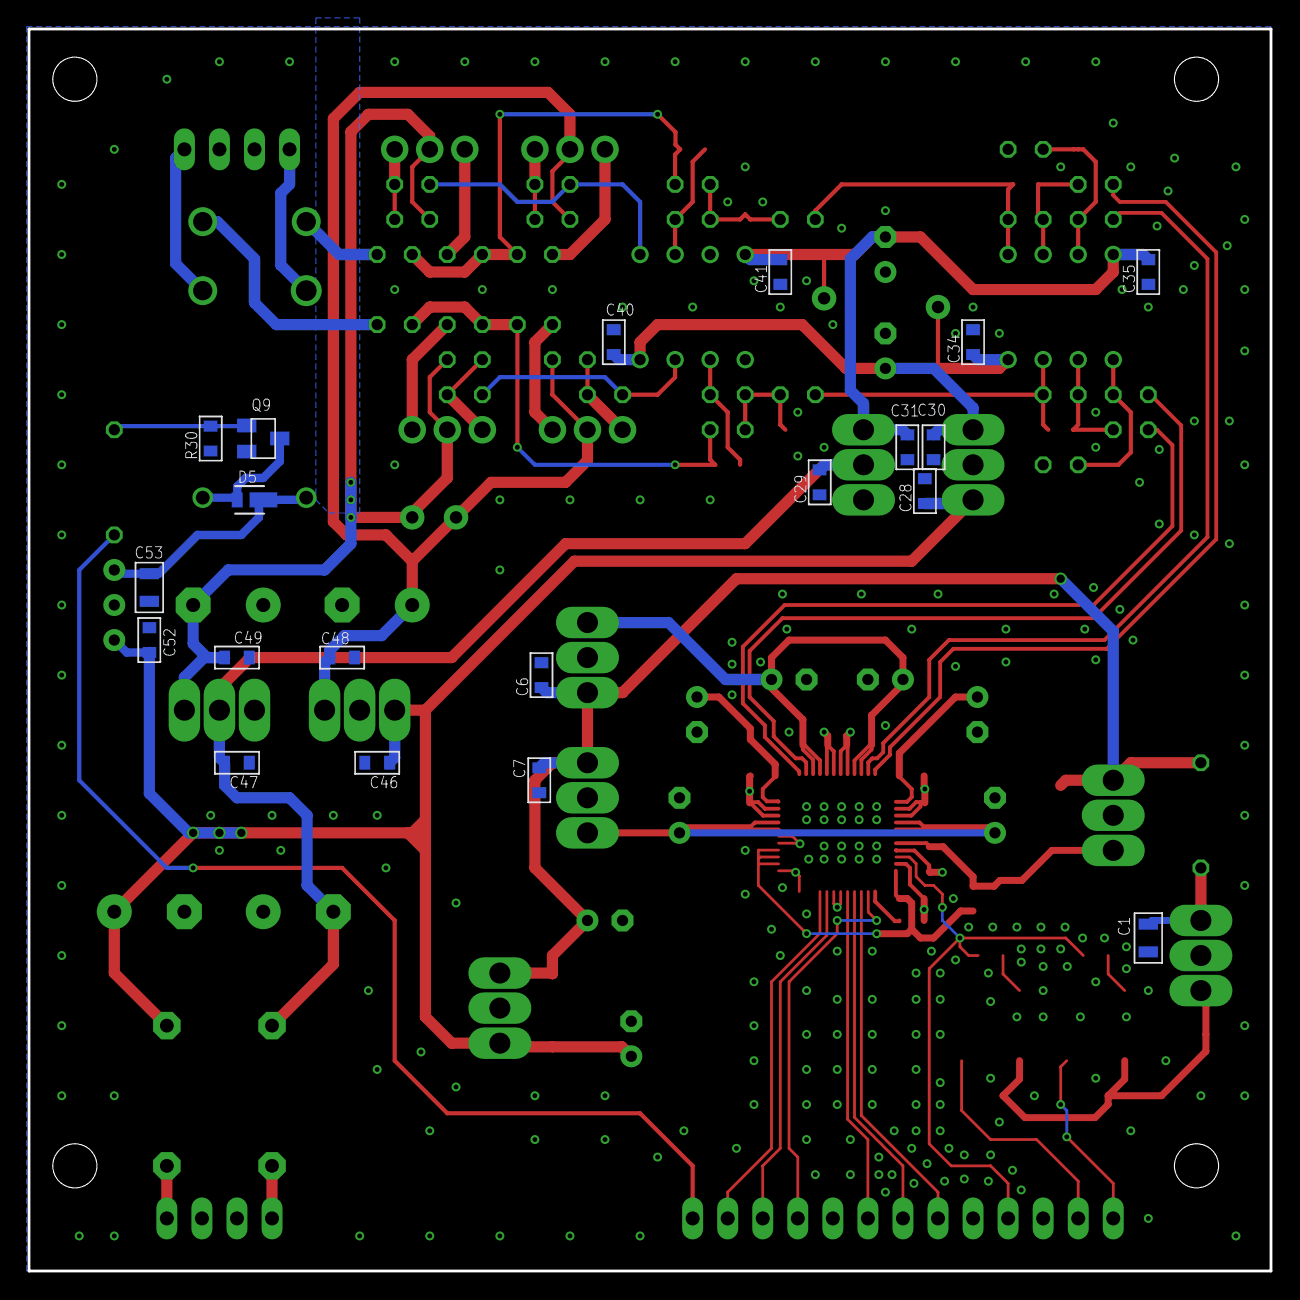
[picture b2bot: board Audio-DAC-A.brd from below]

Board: 2 copper layers, 90.0 x 90.0 mm, 125 parts (20 on the bottom side), 64 nets.
